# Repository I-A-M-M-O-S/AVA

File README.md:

# ROS 2 Jazzy auf dem Jetson

Der kanonische, zuletzt verifizierte Projektstand steht in
[`CURRENT_STATE.md`](CURRENT_STATE.md). Neue Entwickler und Agenten müssen diese
Datei vor Änderungen lesen.

Eine vollständige technische Übergabe für die Fortsetzung mit einer anderen
Instanz steht in [`HANDOFF.md`](HANDOFF.md).

Diese Umgebung installiert ROS 2 Jazzy Desktop in einem Ubuntu-24.04-ARM64-
Container. Das Jetson-Hostsystem und seine L4T-Pakete bleiben unverändert.

Start:

```bash
ros2-jazzy
```

Ein einzelner Befehl kann ebenfalls direkt ausgeführt werden:

```bash
ros2-jazzy ros2 pkg list
```

Der dauerhafte Colcon-Arbeitsbereich liegt unter `workspace/`.

## Gazebo Harmonic

Gazebo Harmonic 8 und die ROS-2-Anbindung `ros_gz` sind im Container
installiert. Über das Desktop-Symbol **Gazebo Harmonic** startet die lokale
Teststrecke. Dasselbe geht im Terminal mit:

```bash
gazebo-harmonic
```

Die Strecke liegt unter
`workspace/simulation/worlds/jetson_test_track.sdf`. Für das spätere
Fahrzeugmodell sind außerdem die ROS-Nachrichten `ackermann_msgs` installiert.

Die Teststrecke enthält das Modell `avaj_car` mit den bisher bekannten Maßen:

- Allradantrieb, Ackermann-Lenkung an der Vorderachse
- Radstand: 270 mm
- Spurweite: 245 mm
- Reifen: 80 mm Durchmesser, 36 mm Breite

Der Desktop-Starter aktiviert automatisch die ROS-Gazebo-Brücke. Steuerung und
Odometrie stehen dadurch als `/cmd_vel` und `/odom` zur Verfügung. Beispiel:

```bash
ros2-jazzy ros2 topic pub --once /cmd_vel geometry_msgs/msg/Twist \
  "{linear: {x: 0.8}, angular: {z: 0.25}}"
```

`linear.x` ist die Geschwindigkeit in m/s, `angular.z` die gewünschte
Gierrate in rad/s. Das vorläufige Modell nimmt 3 kg Fahrzeugmasse und eine
Karosserie von 360 x 190 x 60 mm an; diese Werte sollten später mit den echten
Abmessungen ersetzt werden.

### Live-Steuerung mit WASD

Gazebo starten und danach in einem zweiten Terminal die Tastatursteuerung
oeffnen:

```bash
wasd-drive
```

`wasd-drive` startet die komplette manuelle Testkette:

```text
wasd_teleop -> /control/manual_cmd -> drive_commander
             -> /drive_commands -> usb_bridge -> USB-Serial
```

Der WASD-Node veröffentlicht mit 50 Hz ausschließlich
`/control/manual_cmd` (`rc_car_interfaces/msg/DriveRequest`). Die Fahrwerte
liegen zwischen -100 und +100:

- `steering`: -100 = ganz links, 0 = gerade, +100 = ganz rechts
- `speed`: -100 = voll rueckwaerts, 0 = Stopp, +100 = voll vorwaerts

Im Steuerfenster werden die Tasten gehalten: `W` setzt vorwaerts auf +100, `S`
rueckwaerts auf -100, `A` links auf -100 und `D` rechts auf +100. Beim Loslassen
springt die jeweilige Achse sofort auf 0 zurueck. Dadurch funktionieren auch
Kombinationen wie `W+A`. `Q` oder Escape beendet die Steuerung. Wenn das
Steuerfenster den Tastaturfokus verliert, wird aus Sicherheitsgruenden sofort
neutralisiert. Der `drive_commander` ergänzt Zeitstempel, Sequenz und die
separate Sicherheitsfreigabe. Er ist der einzige Publisher von
`/drive_commands` (`rc_car_interfaces/msg/DriveCommand`). Der Gazebo-Konverter
abonniert ebenfalls nur dieses finale Topic.

Der aktuelle `manual_usb_test.launch.py` ist absichtlich ein reiner
Ausgabetest: ROS-Quellenwatchdog, USB-Nachrichtenwatchdog und ESP-Rückkanal sind
deaktiviert. Solange dieser Testmodus verwendet wird, dürfen Motorcontroller
und Lenkservo nicht angeschlossen beziehungsweise nicht mit Leistung versorgt
werden.

Die autonome Kette startet sicher (USB zunächst Dry-Run) mit:

```bash
ros2-jazzy ros2 launch avaj_car_control autonomous_drive.launch.py
```

Der `control_center` veröffentlicht ausschließlich
`/control/autonomous_cmd`. `mode_manager`, `safety_watchdog` und
`drive_commander` entscheiden getrennt über Auswahl und Freigabe. Manuelle und
autonome Launches nicht gleichzeitig starten.

Die Testlogik besitzt noch keinen abstandsabhängigen Kollisionsstopp und ist
nur für Gazebo-Tests vorgesehen.

### ESP32-USB-Bridge

Die Bridge abonniert ausschließlich `/drive_commands` und erzeugt ein lesbares,
CRC-gesichertes Protokoll:

```bash
ros2-jazzy ros2 run rc_car_usb_bridge usb_bridge
ros2-jazzy ros2 topic echo /drive_usb/tx
ros2-jazzy ros2 topic echo /drive_usb/status
```

Ein Frame sieht beispielsweise so aus:

```text
CMD,42,30,-20,1*887F
```

Der Entwicklungscontainer erhält dynamischen Zugriff auf USB-CDC-Geräte
(`/dev/ttyACM*`) und USB-Serial-Adapter (`/dev/ttyUSB*`). Es gibt absichtlich
keine feste Gerätebindung. Der manuelle Ersttest filtert nach der physischen
USB-Topologie `1-2.2`. Das ist die freie Buchse im selben physischen
Doppel-USB-A-Block wie die Apple-Tastatur (`1-2.1`).
Die Bridge wartet, bis dort genau ein serielles Gerät erscheint.

Topologie eines eingesteckten Adapters kontrollieren:

```bash
for tty in /sys/class/tty/ttyACM* /sys/class/tty/ttyUSB*; do
  test -e "$tty" && readlink -f "$tty/device"
done
```

Falls der tatsächlich verwendete Anschluss nicht `1-2.2` enthält:

```bash
wasd-drive usb_physical_port:=GEFUNDENER_USB_PFAD
```

Ein USB-A-Port ist ein USB-Host und erzeugt ohne eingestecktes
USB-Serial-Gerät keinen seriellen Datenstrom. Für PuTTY auf einem Laptop ist
deshalb ein USB-Serial-Endpunkt erforderlich; eine direkte USB-A-zu-USB-A-
Verbindung zwischen Jetson und Laptop ist nicht zulässig.

Debugging:

```bash
ros2-jazzy ros2 topic echo /control/manual_cmd --no-daemon --spin-time 8
ros2-jazzy ros2 topic info /drive_commands --verbose
ros2-jazzy ros2 topic echo /drive_commands --no-daemon --spin-time 8
ros2-jazzy ros2 topic echo /drive_usb/tx --no-daemon --spin-time 8
ros2-jazzy ros2 topic echo /drive_usb/status --no-daemon --spin-time 8
```

`ros2-jazzy` erzeugt fuer jeden Aufruf einen neuen, kurzlebigen Docker-
Container. Dessen ROS-Discovery-Cache ist beim Start leer. Ein normales
`ros2 topic echo` kann deshalb faelschlich melden, dass ein nachweislich
laufendes Topic nicht publiziert werde oder dass sein Typ unbekannt sei. Fuer
Topic-Abfragen in diesem Projekt deshalb `--no-daemon --spin-time 8`
verwenden. Damit wartet das CLI ohne veralteten Daemon-Cache bis zu acht
Sekunden auf die DDS-Erkennung. Dieses Kommando wurde fuer `/drive_commands`
im laufenden manuellen Stack erfolgreich geprueft.

Für `/drive_commands` muss im normalen Betrieb `Publisher count: 1` gelten;
der Publisher muss `/drive_commander` sein.

**Noch zwingend umzusetzen, bevor Motoren angeschlossen werden:** Watchdogs
wieder aktivieren, ESP-ACK/Status auf `/vehicle/status` implementieren,
Encoderüberwachung ergänzen und einen unabhängigen Command-Timeout im ESP
testen. Der aktuelle Einwegmodus erwartet bewusst keine Antwort.

### Simulierte Sensoren

Das Modell besitzt Sensoren an den angegebenen Montagepositionen:

- Kamera mittig vorne, 6 cm über Boden, Blick geradeaus
- STL27-LiDAR mittig vorne, 10 cm über Boden, Orientierung 90 Grad rechts
- BNO085 aufrecht in der Fahrzeugmitte

Simulation und reale Hardware verwenden dieselbe Treibergrenze. Es darf immer
nur ein Profil die gemeinsamen Rohdaten-Topics publizieren:

- `/camera/image_raw` und `/camera/camera_info`
- `/scan_raw`, aufbereitet als `/scan`
- `/imu/data_raw`, validiert als `/imu/data`

Die Kamera simuliert zunächst 640 x 360 Pixel mit 20 Hz, der LiDAR 720 Strahlen
mit 10 Hz und die IMU 100 Hz. Diese moderaten Werte halten die Simulation auf
dem Jetson flüssig.

Eine andere Welt kann direkt über die ROS-2-Umgebung gestartet werden:

```bash
ros2-jazzy gz sim /workspace/simulation/worlds/eigene_strecke.sdf
```

## STL-27L

Der STL-27L-Treiber veröffentlicht `sensor_msgs/msg/LaserScan` unter
`/scan_raw`. Der gemeinsame Preprocessor stellt anschließend `/scan` bereit.

```bash
docker compose -f /home/avaj/ros2_jazzy/compose.yaml up -d lidar
ros2-jazzy ros2 topic echo /scan --once
```

## Arducam UC-852

Die USB-UVC-Kamera läuft als dauerhafter Dienst mit 1280 x 720 Pixeln,
MJPEG-Eingang und 30 FPS. Sie veröffentlicht:

- `/camera/image_raw` (`sensor_msgs/msg/Image`, RGB8)
- `/camera/camera_info` (`sensor_msgs/msg/CameraInfo`)

Start und Prüfung:

```bash
docker compose -f /home/avaj/ros2_jazzy/compose.yaml up -d camera
ros2-jazzy ros2 topic hz /camera/image_raw
ros2-jazzy ros2 topic echo /camera/camera_info --once
```

Bild anzeigen:

```bash
ros2-jazzy ros2 run rqt_image_view rqt_image_view /camera/image_raw
```

Die Kameraparameter stehen in `config/uc852.yaml`. Die geometrische
Kalibrierung ist noch nicht durchgeführt; deshalb sind die Werte in
`/camera/camera_info` zunächst unkalibriert.

## BNO085 IMU

Der BNO085 ist über den 40-Pin-I²C-Anschluss verbunden:

- Pin 1: 3,3 V
- Pin 6: GND
- Pin 3: SDA
- Pin 5: SCL

Auf diesem Jetson ist das `/dev/i2c-7`; der Sensor verwendet Adresse `0x4A`.
Der dauerhafte IMU-Dienst veröffentlicht mit 100 Hz Rohdaten; der gemeinsame
Preprocessor validiert sie für die kanonische Schnittstelle:

- `/imu/data_raw` -> `/imu/data` (`sensor_msgs/msg/Imu`, Frame `imu_link`)
- `/imu/mag` (`sensor_msgs/msg/MagneticField`, Einheit Tesla)

Start und Prüfung:

```bash
docker compose -f /home/avaj/ros2_jazzy/compose.yaml up -d imu
ros2-jazzy ros2 topic echo /imu/data --once
ros2-jazzy ros2 topic hz /imu/data
```

Die Einstellungen stehen in `config/bno085.yaml`.

IMU und Magnetfeld in RViz anzeigen:

```bash
ros2-jazzy rviz2 -d /config/bno085.rviz
```

## USB-Hotplug

Die Arducam UC-852 und der STL27L werden anhand ihrer eindeutigen USB-IDs
automatisch verwaltet:

- Einstecken der Kamera startet den Dienst `camera`.
- Abziehen der Kamera stoppt nur den Dienst `camera`.
- Einstecken des LiDAR startet den Dienst `lidar`.
- Abziehen des LiDAR stoppt nur den Dienst `lidar`.

Die udev-Regeln und die systemd-Vorlage liegen zusätzlich im Projektordner
`hotplug/`. Systemmeldungen lassen sich so anzeigen:

```bash
journalctl -t ros2-sensor-hotplug
```

## LiDAR-SLAM und Kartierung

Das Paket `avaj_slam` verwendet dieselbe SLAM-Anwendung für Gazebo und das
reale Fahrzeug. Es veröffentlicht den gemeinsamen TF-Baum für Fahrzeug und
Sensoren, startet `slam_toolbox` und bindet in der Simulation die Gazebo-
Odometrie über `robot_localization` an.

Zuerst Gazebo neu starten, damit die `/clock`-Bridge aus der aktuellen
Konfiguration geladen wird. Danach die SLAM-Anwendung für die Simulation
starten:

```bash
gazebo-harmonic
ros2-jazzy ros2 launch avaj_slam slam.launch.py simulation:=true use_sim_time:=true
```

Die Strecke anschließend mit `wasd-drive` langsam abfahren. Für die Karte
werden die Simulationsdaten automatisch auf die gemeinsamen SLAM-Topics
abgebildet:

```text
/scan_raw      -> /scan
/imu/data_raw  -> /imu/data
/odom          -> robot_localization -> odom -> base_link
```

Der vollständige Node- und Topic-Vertrag steht in
[`docs/ros_graph.md`](docs/ros_graph.md).

Karte speichern:

```bash
ros2-jazzy ros2 run avaj_slam save_map.sh /workspace/maps/teststrecke
```

Das erzeugt `teststrecke.yaml` und `teststrecke.pgm` im persistenten
Workspace. Für das reale Fahrzeug wird derselbe Startpunkt verwendet:

```bash
ros2-jazzy ros2 launch avaj_slam slam.launch.py real:=true
```

Dafür müssen `/scan`, eine Odometrie mit `odom`/`base_link` und der reale
LiDAR-TF vorhanden sein. Die Kamera wird für 2D-LiDAR-SLAM nicht benötigt.

### Experimenteller Nav2-Test während Online-SLAM

Wenn Gazebo und der obige AVAJ-SLAM-Launch laufen und `/map` publiziert wird,
können die installierten Nav2-Standardserver und die Nav2-RViz-Oberfläche in
zwei weiteren Terminals gestartet werden:

```bash
ros2-jazzy ros2 launch nav2_bringup navigation_launch.py use_sim_time:=true
ros2-jazzy ros2 launch nav2_bringup rviz_launch.py use_sim_time:=true
```

In RViz `map` als Fixed Frame wählen und mit `Nav2 Goal` ein Ziel setzen.
Nicht zusätzlich `nav2_bringup bringup_launch.py slam:=true` starten, weil
bereits `avaj_slam` den einzigen SLAM-Publisher für `map -> odom` stellt.
WASD und der manuelle Drive-Stack dürfen ebenfalls nicht parallel laufen:
Nav2 publiziert in diesem vorläufigen Profil direkt `/cmd_vel`.

Dieser Ablauf verwendet noch Nav2-Stockparameter. Fahrzeugkontur,
Ackermann-Controller, Geschwindigkeits-/Beschleunigungsgrenzen, Costmaps und
Zielnavigation sind nicht AVAJ-spezifisch validiert. Ein Profil für
gespeicherte Karten und AMCL ist noch nicht implementiert.

Der physische BNO085 bleibt fest an `/dev/i2c-7` angeschlossen und muss für
Gazebo nicht entfernt werden. Die Simulation nutzt ihn derzeit nicht im EKF;
dieser fusioniert ausschließlich Gazebos `/odom`.

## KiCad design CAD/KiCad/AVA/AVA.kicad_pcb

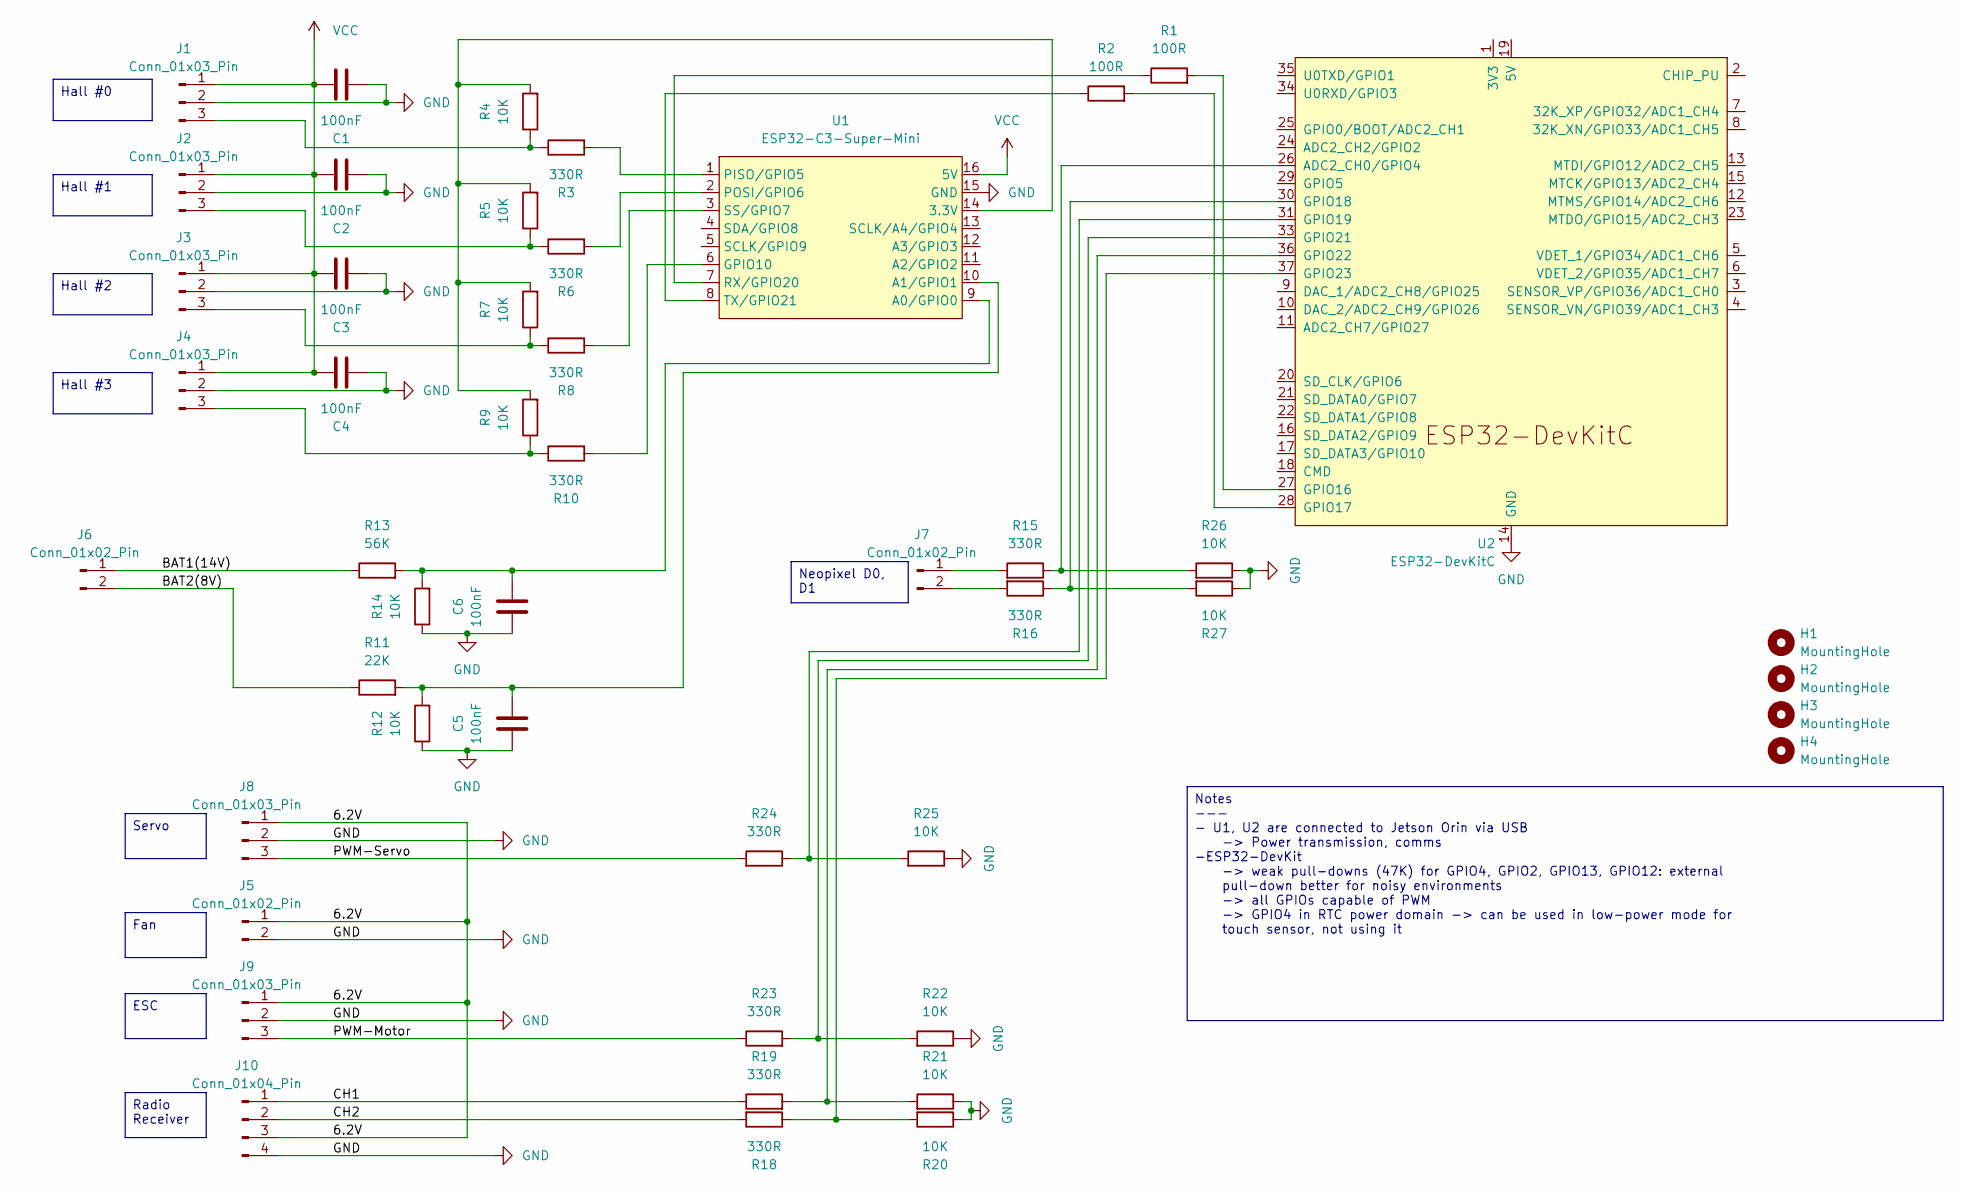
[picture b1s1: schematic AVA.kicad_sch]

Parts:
C1, C2, C3, C4, C5, C6: 100nF; C_Disc_D5.0mm_W2.5mm_P5.00mm
H1, H2, H3, H4: MountingHole; MountingHole_3.2mm_M3
J1, J2, J3, J4, J8, J9: Conn_01x03_Pin; PinSocket_1x03_P2.54mm_Vertical
J5, J6, J7: Conn_01x02_Pin; PinSocket_1x02_P2.54mm_Vertical
J10: Conn_01x04_Pin; PinSocket_1x04_P2.54mm_Vertical
R1, R2: 100R; R_Axial_DIN0207_L6.3mm_D2.5mm_P10.16mm_Horizontal
R3, R6, R8, R10, R15, R16, R18, R19, R23, R24: 330R; R_Axial_DIN0207_L6.3mm_D2.5mm_P10.16mm_Horizontal
R4, R5, R7, R9, R12, R14, R20, R21, R22, R25, R26, R27: 10K; R_Axial_DIN0207_L6.3mm_D2.5mm_P10.16mm_Horizontal
R11: 22K; R_Axial_DIN0207_L6.3mm_D2.5mm_P10.16mm_Horizontal
R13: 56K; R_Axial_DIN0207_L6.3mm_D2.5mm_P10.16mm_Horizontal
U1: ESP32-C3-Super-Mini
U2: ESP32-DevKitC

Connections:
/6.2V: J5.1, J8.1, J9.1, J10.3
/BAT1(14V): J6.1, R13.1
/BAT2(8V): J6.2, R11.1
/CH1: J10.1, R19.1
/CH2: J10.2, R18.2
/PWM-Motor: J9.3, R23.1
/PWM-Servo: J8.3, R24.2
GND: C1.2, C2.2, C3.2, C4.2, C5.1, C6.1, J1.2, J2.2, J3.2, J4.2, J5.2, J8.2, J9.2, J10.4, R12.1, R14.1, R20.1, R21.1, R22.1, R25.1, R26.1, R27.1, U1.15 (GND), U2.14 (GND), U2.32 (GND), U2.38 (GND)
unnamed: J1.3, R3.1, R4.1
unnamed: J2.3, R5.1, R6.1
unnamed: J3.3, R7.1, R8.1
unnamed: J4.3, R9.1, R10.1
unnamed: J7.1, R15.2
unnamed: J7.2, R16.2
unnamed: R4.2, R5.2, R7.2, R9.2, U1.14 (3.3V)
unnamed: C6.2, R13.2, R14.2, U1.9 (A0/GPIO0)
unnamed: C5.2, R11.2, R12.2, U1.10 (A1/GPIO1)
unnamed: R10.2, U1.6 (GPIO10)
unnamed: R3.2, U1.1 (PISO/GPIO5)
unnamed: R6.2, U1.2 (POSI/GPIO6)
unnamed: R1.1, U1.7 (RX/GPIO20)
unnamed: R8.2, U1.3 (SS/GPIO7)
unnamed: R2.1, U1.8 (TX/GPIO21)
unnamed: R15.1, R26.2, U2.26 (ADC2_CH0/GPIO4)
unnamed: R1.2, U2.27 (GPIO16)
unnamed: R2.2, U2.28 (GPIO17)
unnamed: R16.1, R27.2, U2.30 (GPIO18)
unnamed: R24.1, R25.2, U2.31 (GPIO19)
unnamed: R22.2, R23.2, U2.33 (GPIO21)
unnamed: R19.2, R21.2, U2.36 (GPIO22)
unnamed: R18.1, R20.2, U2.37 (GPIO23)
VCC: C1.1, C2.1, C3.1, C4.1, J1.1, J2.1, J3.1, J4.1, U1.16 (5V)

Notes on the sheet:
Hall #2
Hall #3
Notes --- - U1, U2 are connected to Jetson Orin via USB -> Power transmission, comms -ESP32-DevKit -> weak pull-downs (47K) for GPIO4, GPIO2, GPIO13, GPIO12: external pull-down better for noisy environments -> all GPIOs capable of PWM -> GPIO4 in RTC power domain -> can be used in low-power mode fo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
Fan
Servo
ESC
Hall #0
Neopixel D0, D1
Hall #1
Radio Receiver

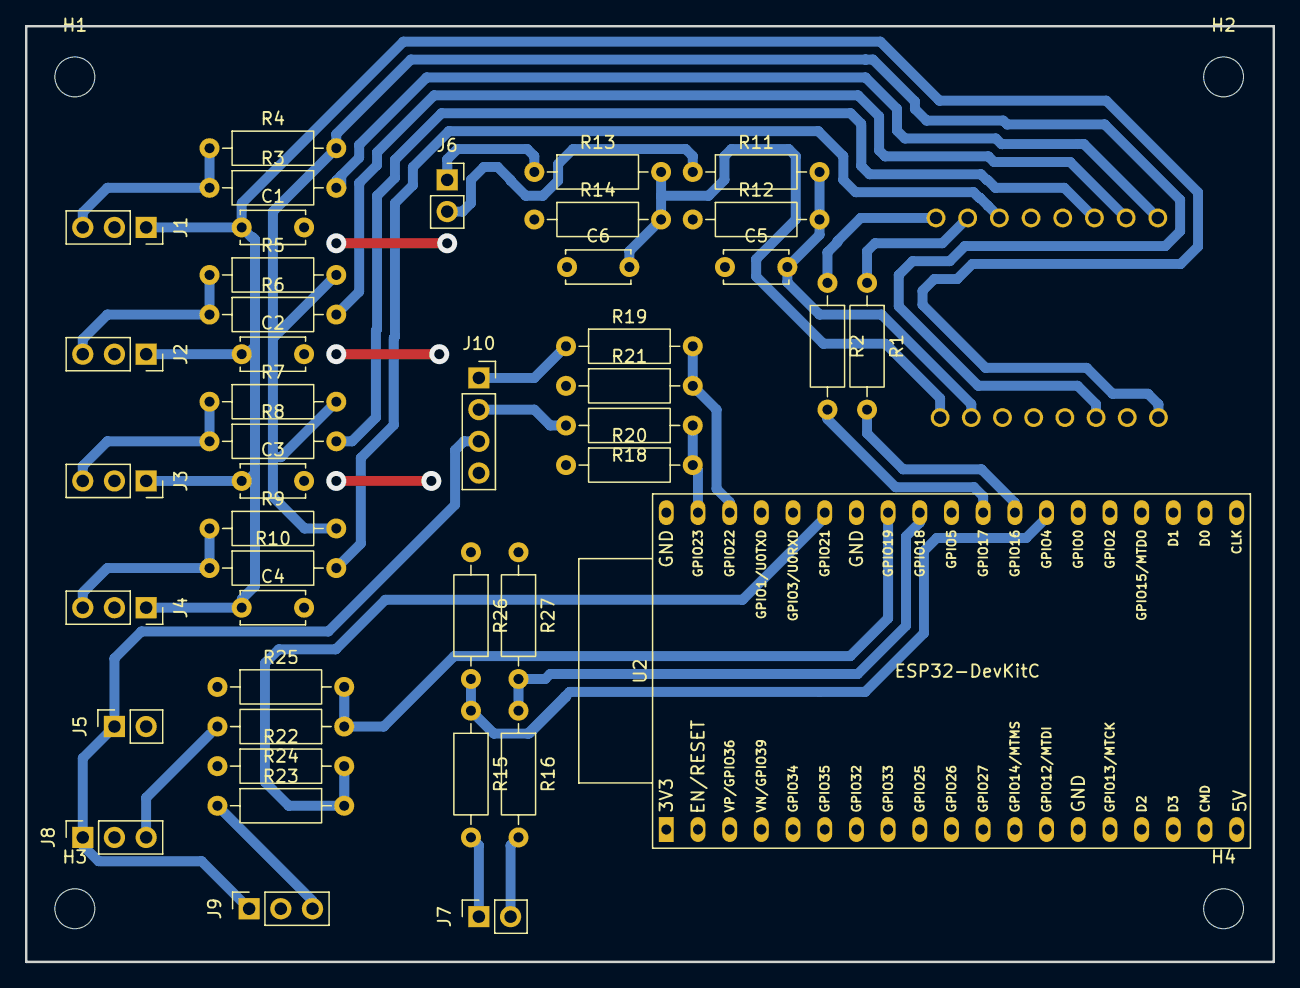
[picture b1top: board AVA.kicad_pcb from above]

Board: 2 copper layers, 100.0 x 75.0 mm, 48 parts (1 on the bottom side), 32 nets.

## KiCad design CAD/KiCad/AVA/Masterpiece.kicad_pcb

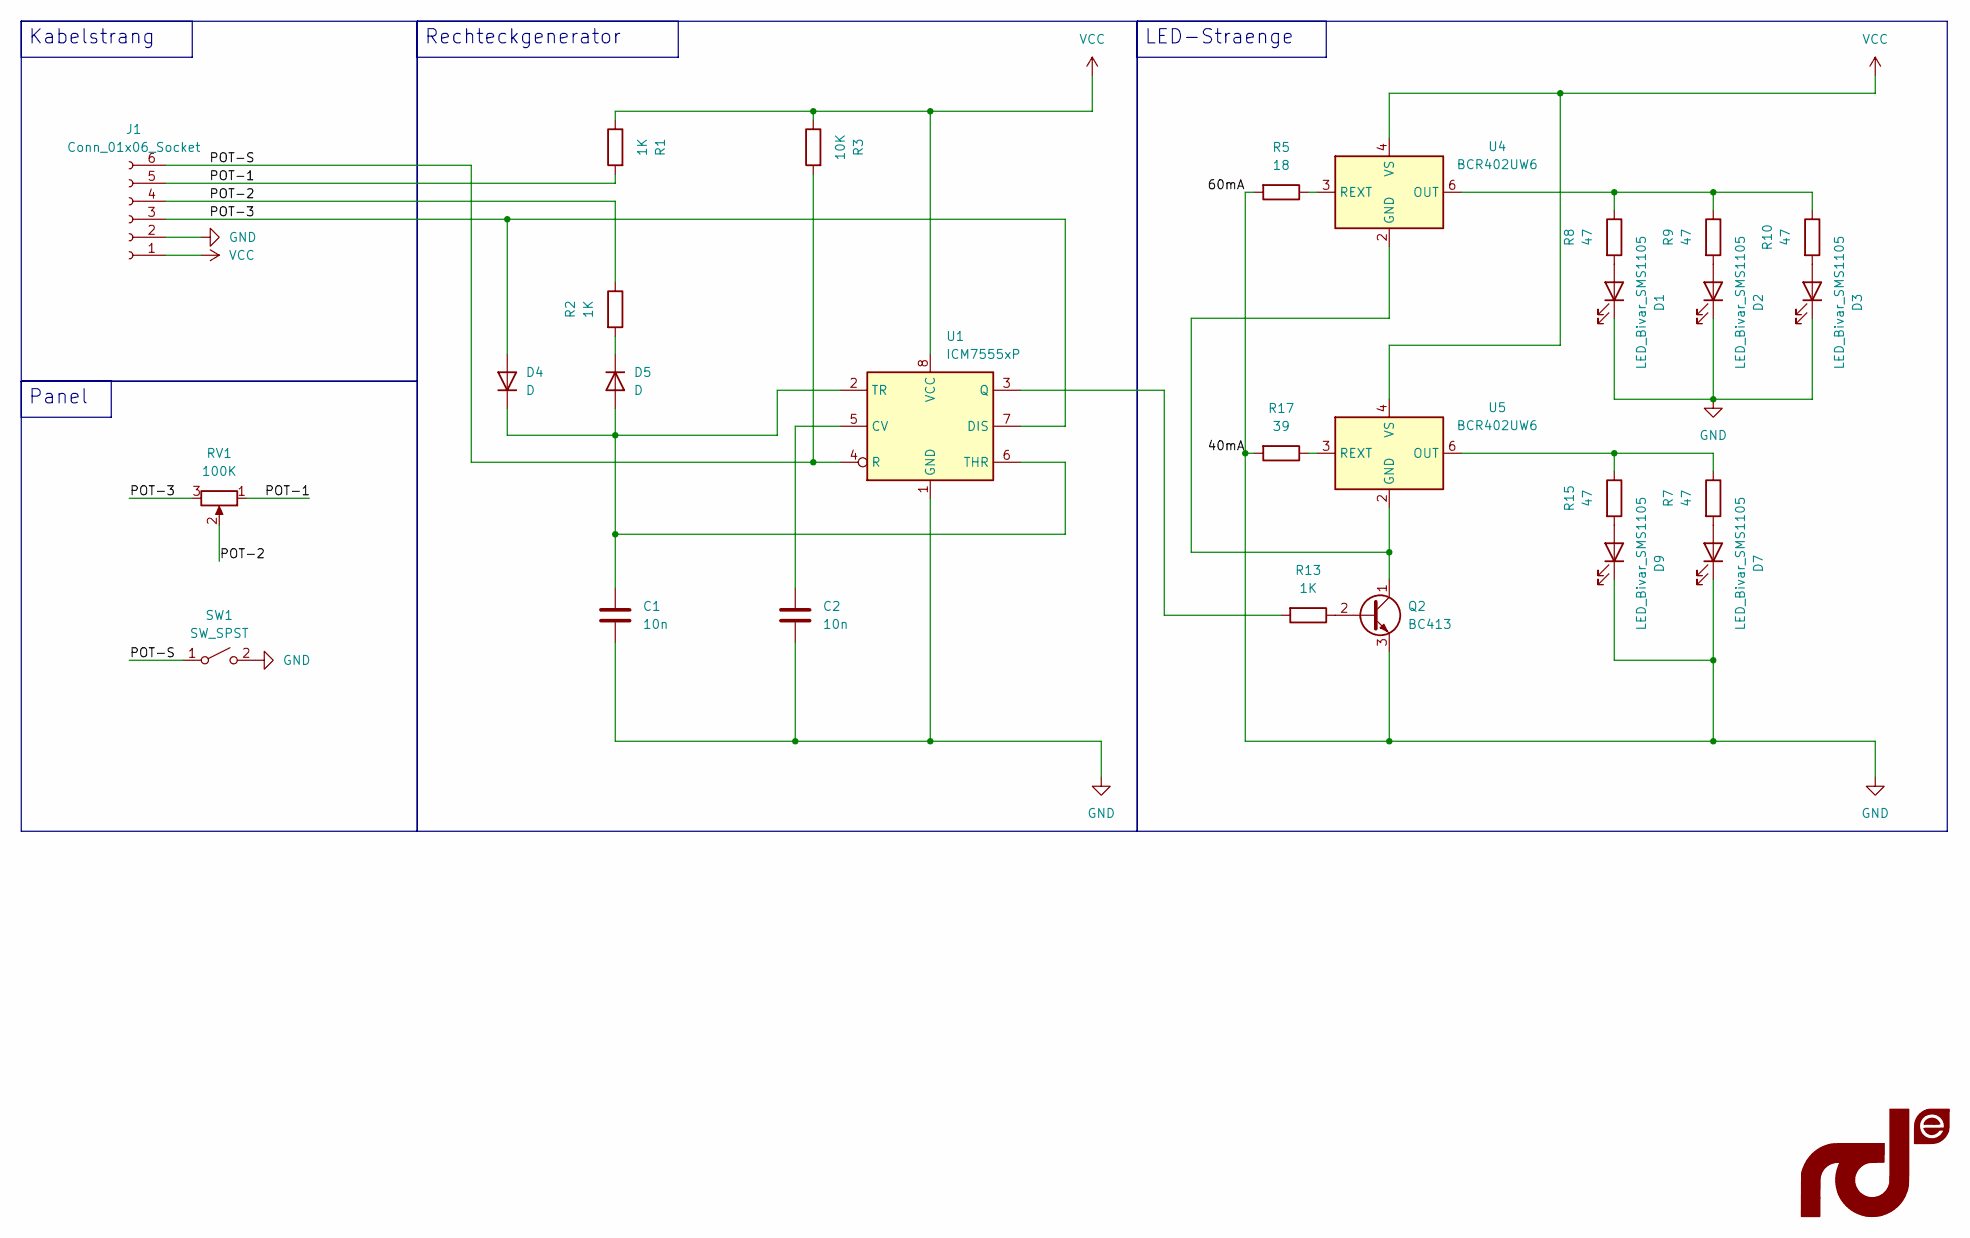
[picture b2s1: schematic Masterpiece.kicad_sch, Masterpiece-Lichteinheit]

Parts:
C1, C2: 10n; C_Disc_D3.4mm_W2.1mm_P2.50mm
D1, D2, D3, D7, D9: LED_Bivar_SMS1105; LED_BIVAR_SMS1105UWDN_OSRAM_2808
D4, D5: D; D_DO-35_SOD27_P7.62mm_Horizontal
J1: Conn_01x06_Socket; SolderWire-0.1sqmm_1x06_P3.6mm_D0.4mm_OD1mm
Q2: BC413; TO-92_Inline
R1, R2, R13: 1K; R_Axial_DIN0207_L6.3mm_D2.5mm_P10.16mm_Horizontal
R3: 10K; R_Axial_DIN0207_L6.3mm_D2.5mm_P10.16mm_Horizontal
R5: 18; R_Axial_DIN0207_L6.3mm_D2.5mm_P10.16mm_Horizontal
R7, R8, R9, R10, R15: 47; R_Axial_DIN0207_L6.3mm_D2.5mm_P10.16mm_Horizontal
R17: 39; R_Axial_DIN0207_L6.3mm_D2.5mm_P10.16mm_Horizontal
RV1: 100K
SW1: SW_SPST
U1: ICM7555xP; DIP-8_W7.62mm
U4, U5: BCR402UW6; SC-74-6_1.55x2.9mm_P0.95mm

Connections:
/POT-1: J1.5, R1.2, RV1.1
/POT-2: J1.4, R2.1, RV1.2
/POT-3: D4.2 (A), J1.3, RV1.3, U1.7 (DIS)
/POT-S: J1.6, R3.2, SW1.1 (A), U1.4 (R)
GND: C1.2, C2.2, D1.2 (K), D2.2 (K), D3.2 (K), D7.2 (K), D9.2 (K), J1.2, Q2.3 (E), R5.2, R17.2, SW1.2 (B), U1.1 (GND)
unnamed: D1.1 (A), R8.2
unnamed: D2.1 (A), R9.2
unnamed: D3.1 (A), R10.2
unnamed: C1.1, D4.1 (K), D5.2 (A), U1.2 (TR), U1.6 (THR)
unnamed: D5.1 (K), R2.2
unnamed: D7.1 (A), R7.2
unnamed: D9.1 (A), R15.2
unnamed: Q2.2 (B), R13.1
unnamed: Q2.1 (C), U4.2 (GND), U5.2 (GND)
unnamed: C2.1, U1.5 (CV)
unnamed: R13.2, U1.3 (Q)
unnamed: R8.1, R9.1, R10.1, U4.6 (OUT)
unnamed: R5.1, U4.3 (REXT)
unnamed: R7.1, R15.1, U5.6 (OUT)
unnamed: R17.1, U5.3 (REXT)
VCC: J1.1, R1.1, R3.1, U1.8 (VCC), U4.4 (VS), U5.4 (VS)

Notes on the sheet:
Kabelstrang
LED-Straenge
Panel
Rechteckgenerator

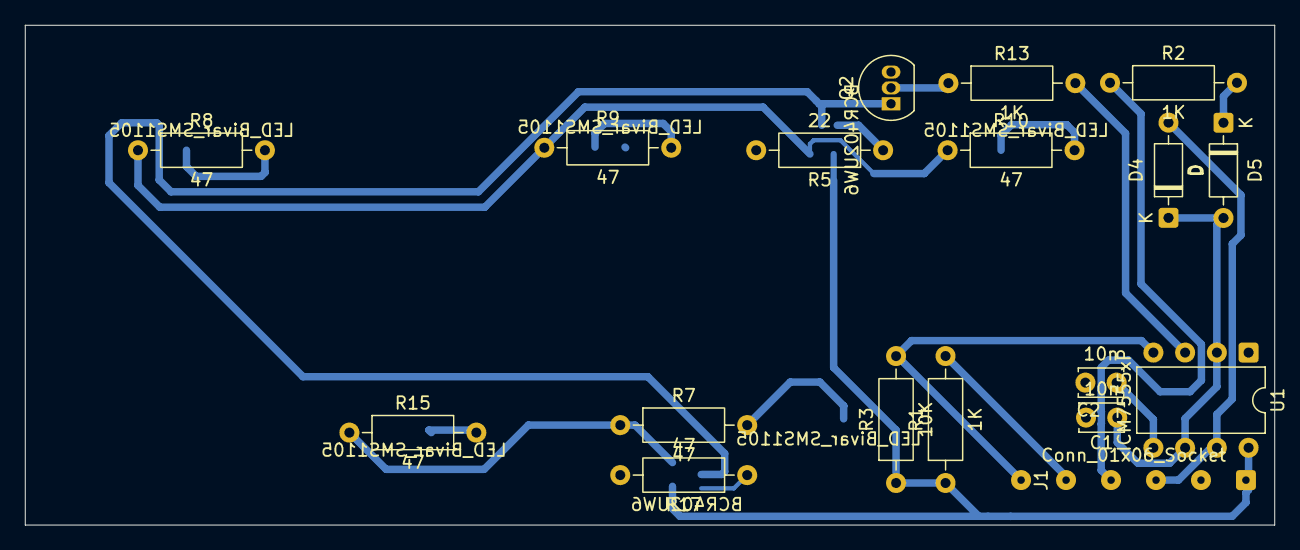
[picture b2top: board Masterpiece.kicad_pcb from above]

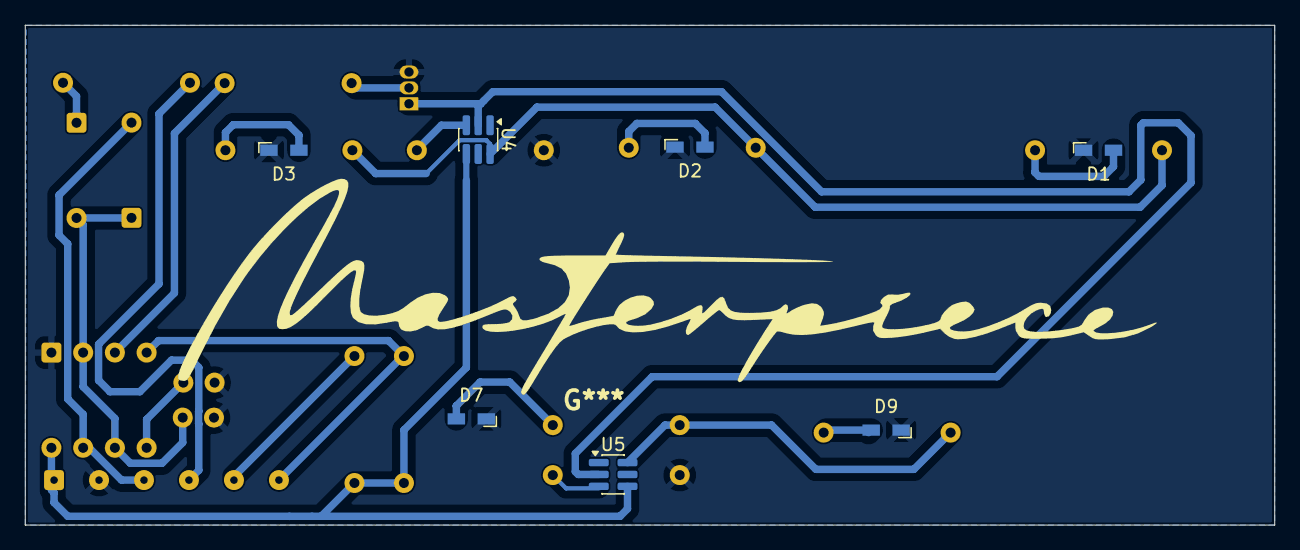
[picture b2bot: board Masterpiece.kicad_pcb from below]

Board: 2 copper layers, 100.0 x 40.0 mm, 25 parts (7 on the bottom side), 21 nets.

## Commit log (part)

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2026-05-15 Base foler structure and few external documents for the start
2026-06-22 Working on schematic.
2026-06-22 Absolutely barebones, borderline starving schematic done. Probably fucked up, earned ciggie break tho
